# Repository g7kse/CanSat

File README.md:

# CanSat

This is a repository for software that can be used for primary and secondary missions

The mission uses RFM9x Lora modules for transmit and receive as well as 2 Raspberry Pi Pico's to handle the data.

A BMP280 breakout provides temperature,pressure and inferred altitude (based on local air pressure)

# Transmitter breadboard layout

# Receiver breadboard layout

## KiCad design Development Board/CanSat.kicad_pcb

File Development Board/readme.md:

# Here you'll find some basic development boards.

The V1.1 boards have been verified and can be obtained very cheaply from JLCPCB

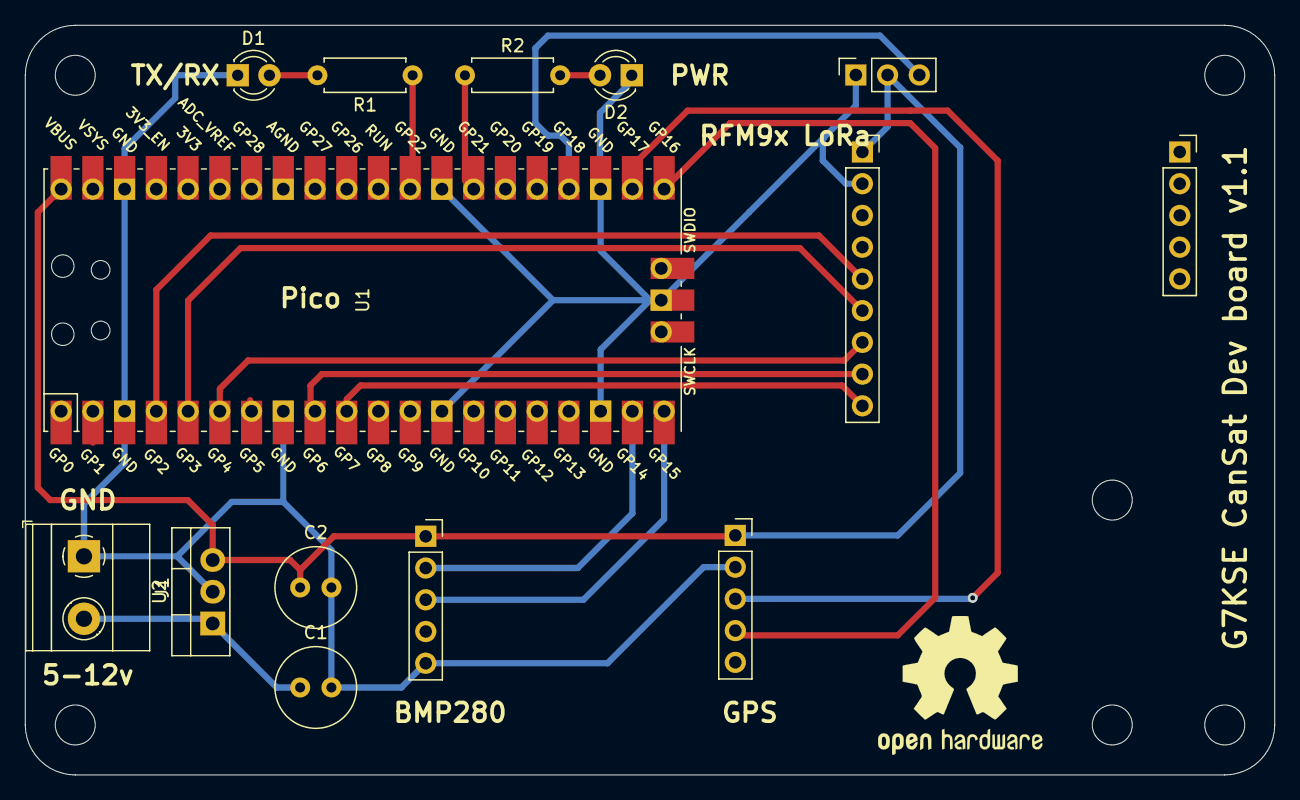
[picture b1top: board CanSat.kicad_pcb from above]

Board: 2 copper layers, 100.0 x 60.0 mm, 13 parts (0 on the bottom side), 17 nets.

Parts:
BMP280: Conn_01x05_Female; PinSocket_1x05_P2.54mm_Vertical
C1: 10uF; C_Radial_D6.3mm_H7.0mm_P2.50mm
C2: 100uF; C_Radial_D6.3mm_H7.0mm_P2.50mm
D1, D2: LED; LED_D3.0mm
GPS1: Conn_01x05_Female; PinSocket_1x05_P2.54mm_Vertical
J1: Screw_Terminal_01x02; TerminalBlock_Phoenix_MKDS-1,5-2_1x02_P5.00mm_Horizontal
R1, R2: 220R; R_Axial_DIN0207_L6.3mm_D2.5mm_P7.62mm_Horizontal
RFM9xLora1: Conn_01x09_Female; PinSocket_1x09_P2.54mm_Vertical
Servo1: Conn_01x03_Male; PinSocket_1x03_P2.54mm_Vertical
U1: Pico; RPi_Pico_SMD_TH
U2: L7805; TO-220-3_Vertical

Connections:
+5V: BMP280.1, C2.1, GPS1.1, RFM9xLora1.1, Servo1.2, U1.40 (VBUS), U2.3 (OUT)
/CS: RFM9xLora1.8, U1.9 (GPIO6)
/MISO: RFM9xLora1.6, U1.5 (GPIO3)
/MOSI: RFM9xLora1.7, U1.6 (GPIO4)
/PWRLED: R1.1, U1.29 (GPIO22)
/RST: RFM9xLora1.9, U1.10 (GPIO7)
/RXD: GPS1.4, U1.21 (GPIO16)
/SCK: RFM9xLora1.5, U1.4 (GPIO2)
/SCL: BMP280.3, U1.20 (GPIO15)
/SDA: BMP280.2, U1.19 (GPIO14)
/Servo: Servo1.3, U1.24 (GPIO18)
/TXD: GPS1.3, U1.22 (GPIO17)
/TXLED: R2.1, U1.27 (GPIO21)
GND: BMP280.5, C1.2, C2.2, D1.1 (K), D2.1 (K), GPS1.2, J1.1, RFM9xLora1.2, Servo1.1, U1.3 (GND), U1.8 (GND), U1.13 (GND), U1.18 (GND), U1.23 (GND), U1.28 (GND), U1.38 (GND), U1.42 (GND), U2.2 (GND)
unnamed: C1.1, J1.2, U2.1 (IN)
unnamed: D1.2 (A), R1.2
unnamed: D2.2 (A), R2.2

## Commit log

2021-12-11 Simple packet receive
    An example that can be used to demonstrate the reception of data packets from the rfm9x module
2021-12-11 Create transmit.py
    Initial commit
2022-06-22 Create transmit_gps.py
    example of code to use gps
2022-09-29 Add files via upload
    V1.1
